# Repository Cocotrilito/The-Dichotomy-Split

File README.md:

# The -Dichotomy- Split

[Download Final Firmware](<BUILD FINAL FIRMWARE PICTURES ETC/FinalFirmware.zip>)

An Split keyboard, created to understand new things like matrix and wireless things, and also from the feeling of being split, Im trying to become someone new but im still stuck in this hole, A tool for the transition... a bridge out of the hole.

## The reason behind this project...
Initially I wanted to prove myself I could go a little more deeper, what I mean Is that I had already made a macropad as my first hackclub project 4 months ago, and the split keyboard was the logical step, when I started with KiCad Fusion and coding.
everything was really hard im not saying today it isnt, but compared to how much I struggled 4 months ago, I can proudly say I have learned, and not just a little, but A LOT, and as I am writing this, throught my headphones KUNGFUPANDA theme song is blasting my
ears, this is the same song I used to play back and back again 4 months ago, and you see 4 months ago I was lost (im still kinda but not as I was), I was heartbroken, and without an actual purpose, and I saw I video on my feed talking about blueprint, this made
me really curious, and I started learning, and now here I am, well I wanted to learn about ZMK in my macropad I only did the QMK firmware but I really wanted to tryout ZMK, and was really cool!, also I wanted to make the projects that I thought were impossible
and to the Isaac of 4 months ago... Thanks!, you have really changed your life, and to the future Isaac... How are you doing? was it all worth it?... thanks for reading if you did! <3

## zmk repo
[ZMK code](https://github.com/Cocotrilito/zmk-config)
## layout

## Schematic Overview

## PCB

<table>
  <tr>
    <td align="center"><br><b>PCB OVERVIEW</b></td>
    <td align="center"><br><b>Render</b></td>
    <td align="center"><br><b>PCB layout</b></td>
  </tr>
  <tr>
    <td align="center"><br><b>PCB Top</b></td>
    <td align="center"><br><b>PCB Back</b></td>
    <td></td>
  </tr>
</table>

## CAD Render

## BOM

| Name | Purpose | Qty | Total Cost (USD) | Link |
| :--- | :--- | :---: | :---: | :--- |
| **1N4148W SOD-123** | Efficiency for pins in matrix, also avoids ghosting | 1 (set) | $1.31 | [AliExpress](https://www.aliexpress.us/item/3256810466885186.html) |
| **XDA Profile PBT Keycaps** | Ergonomics and feel | 1 (set) | $11.83 | [AliExpress](https://www.aliexpress.us/item/3256810402164930.html) |
| **Outemu Silent Switches** | Mechanical input (Tactile/Silent) | 1 (set) | $7.55 | [AliExpress](https://www.aliexpress.us/item/3256811652574937.html) |
| **LEDs SK6812 MINI-E** | Per-key RGB lighting (WS2812B compatible) | 1 (set) | $4.83 | [AliExpress](https://www.aliexpress.us/item/3256810305129996.html) |
| **PCB Manufacturing** | Custom designed PCBs for the split layout | 1 (set) | $14.60 | [JLCPCB] |
| **Seeed Studio XIAO nRF52840** | Main microcontrollers with BLE for wireless | 2 | $37.98 | [Amazon](https://www.amazon.com/gp/product/B09T9VVQG7/) |

## SPECIAL THANKS!
Thanks for reading! made possible with [STASIS by HackClubbers](http://stasis.hackclub.com/)

## You might also like!
[Voyager Panel](https://github.com/Cocotrilito/Voyager-Panel)
[HALO-0](https://github.com/Cocotrilito/HALO-0)

## final thanks :3
By cocotrilo made with luv (THIS ONE WAS WITH philosophical meaning) keep the grind <3

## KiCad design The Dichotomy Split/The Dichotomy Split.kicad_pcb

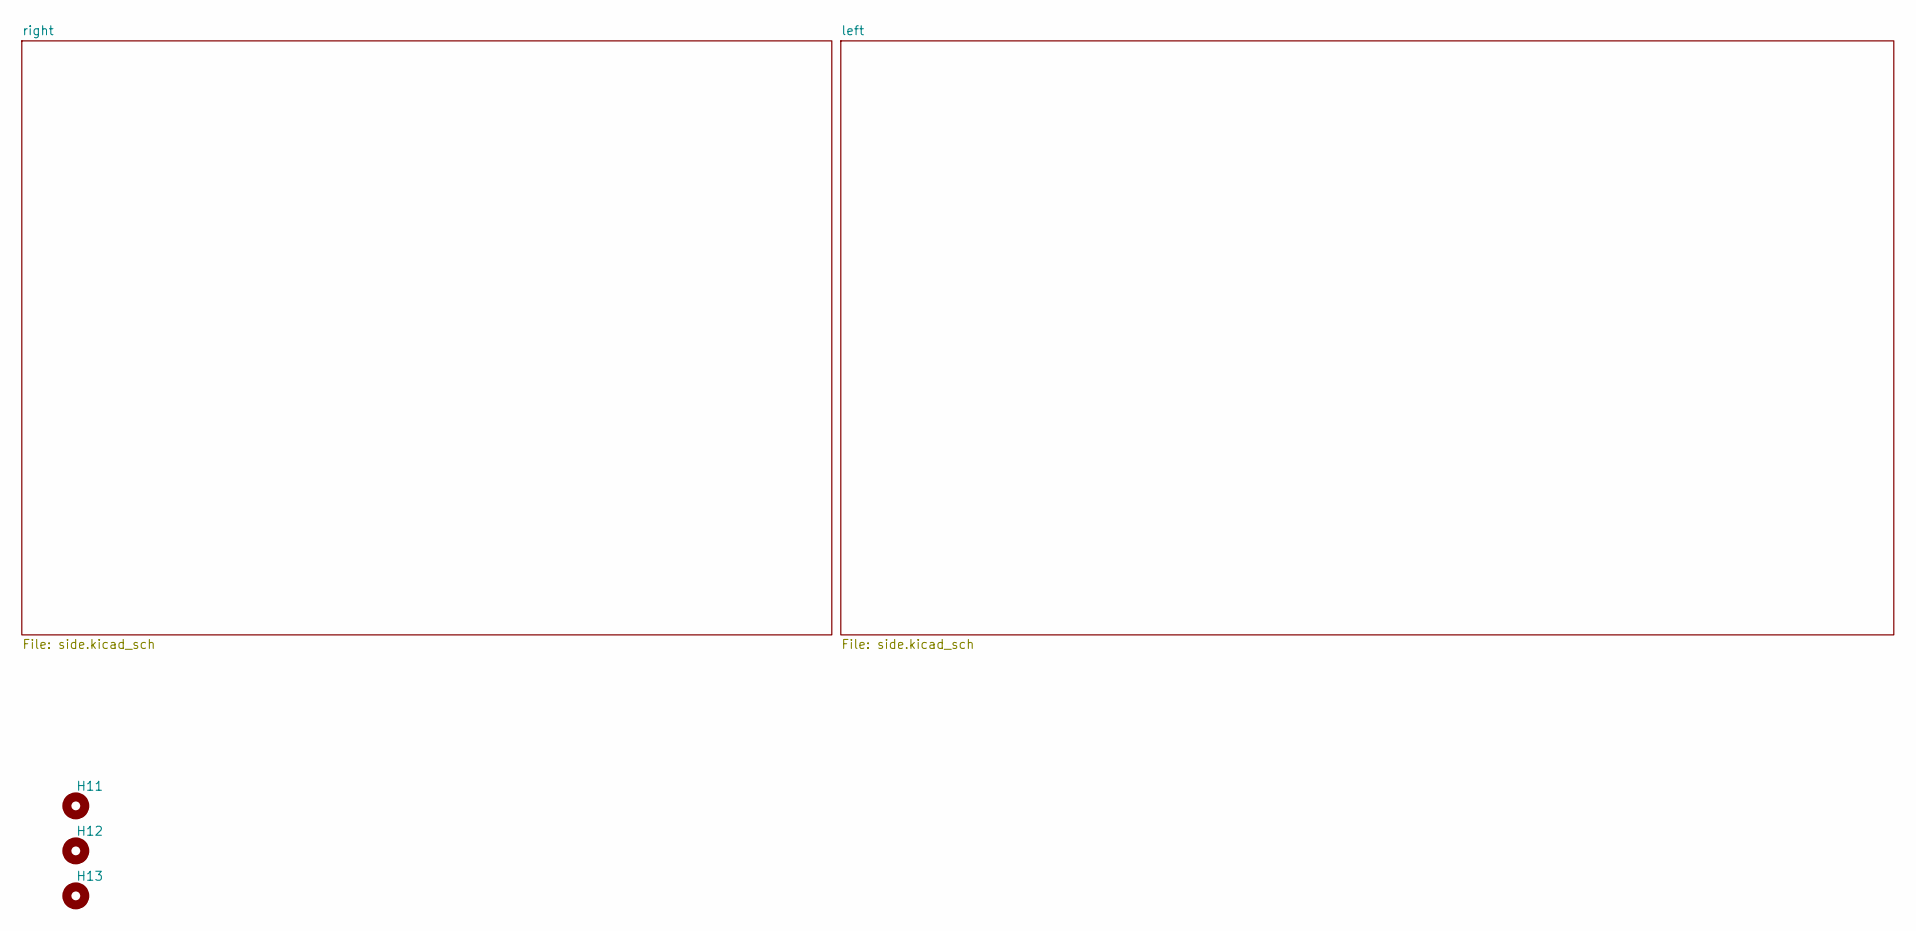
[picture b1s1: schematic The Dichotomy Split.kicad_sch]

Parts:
H11, H12, H13: MountingHole; mouse-bite-5mm-slot

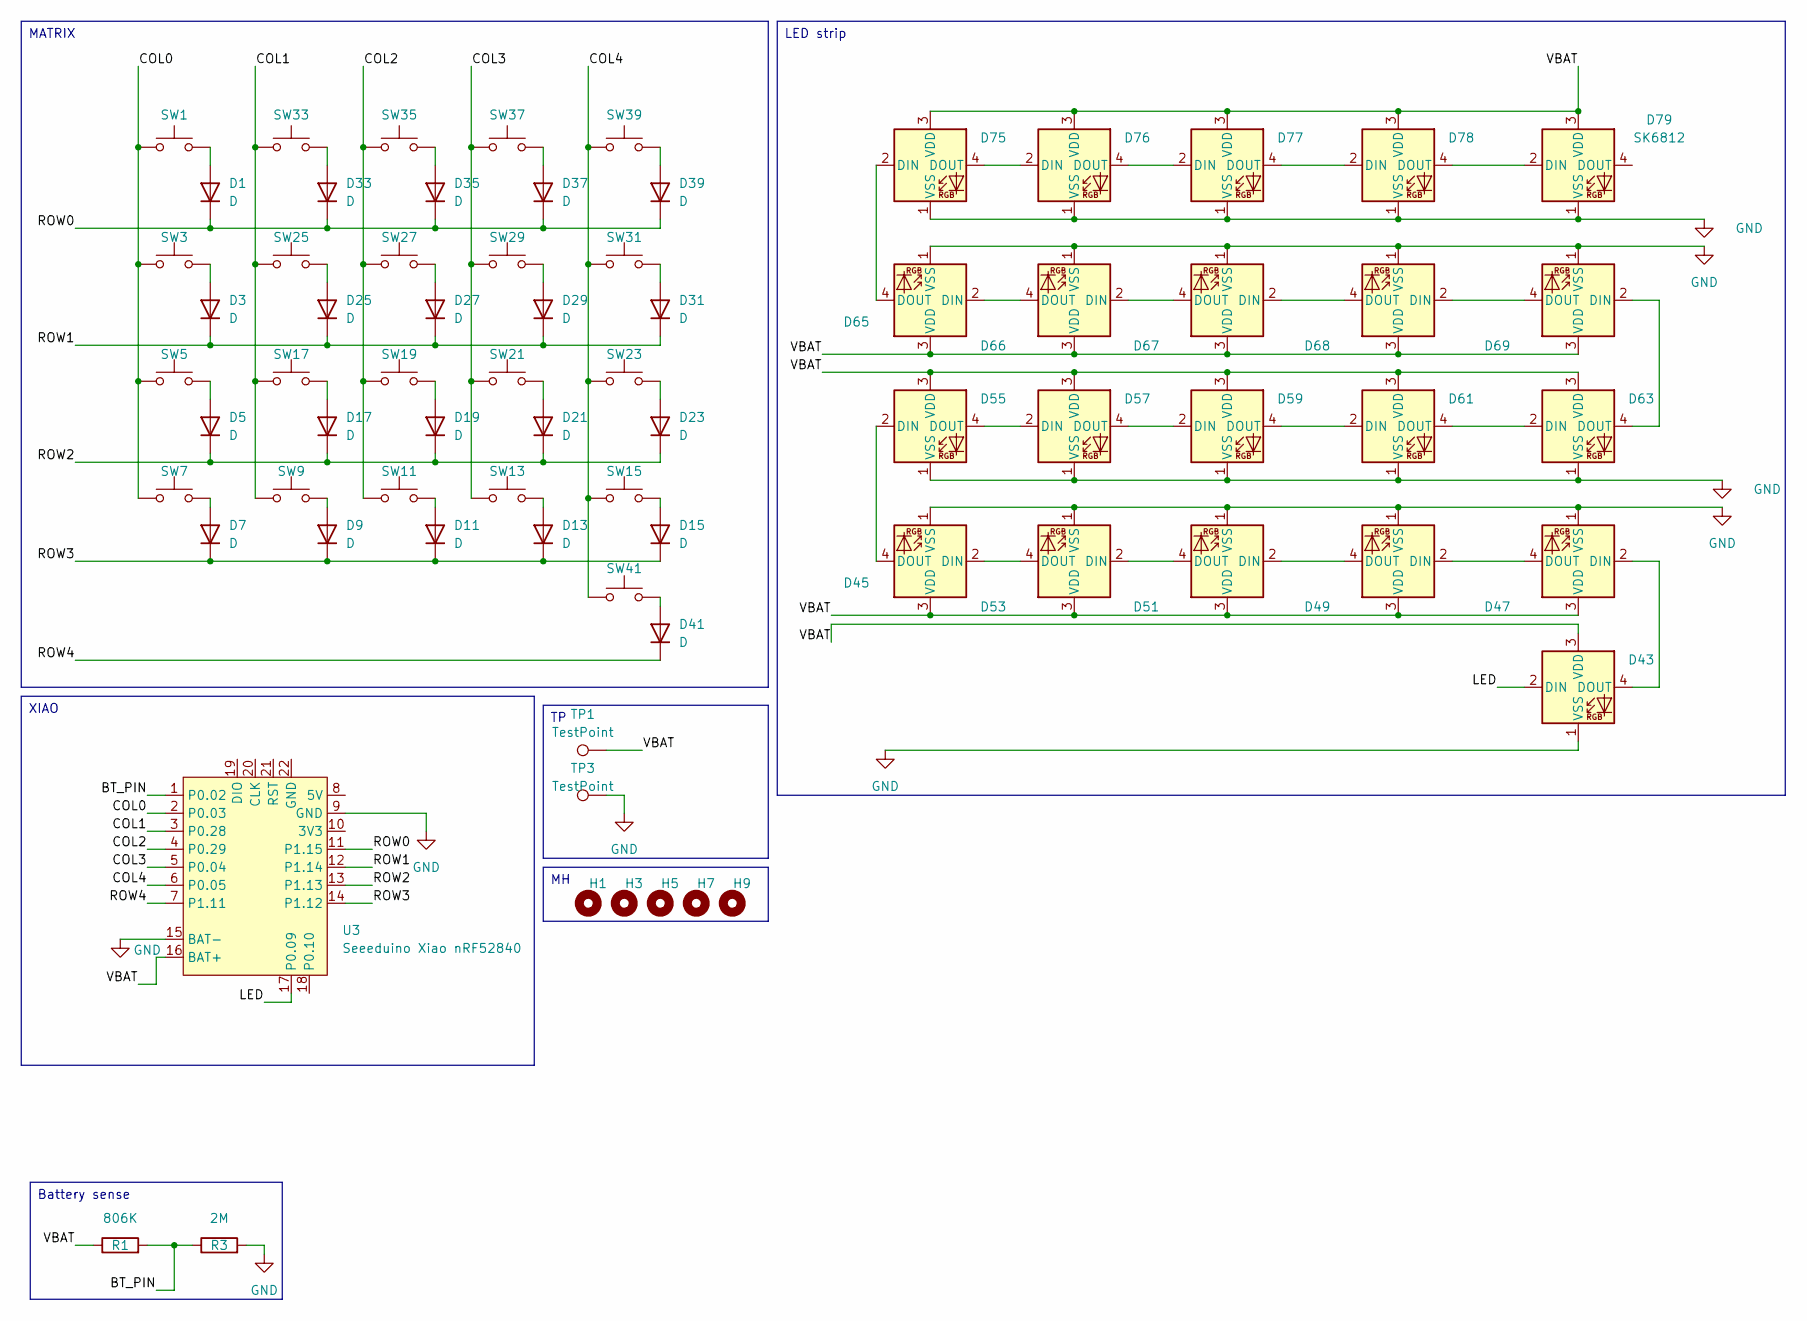
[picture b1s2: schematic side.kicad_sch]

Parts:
D1, D3, D5, D7, D9, D11, D13, D15, D17, D19, D21, D23, D25, D27, D29, D31, D33, D35, D37, D39, D41: D; D_SOD-123
D43, D45, D47, D49, D51, D53, D55, D57, D59, D61, D63, D65, D66, D67, D68, D69, D75, D76, D77, D78, D79: SK6812; LED_SK6812MINI-E_3.2x2.8mm_P1.5mm_ReverseMount
H1, H3, H5, H7, H9: MountingHole; MountingHole_3.2mm_M3_DIN965_Pad
R1: 806K; R_0805_2012Metric
R3: 2M; R_0805_2012Metric
SW1, SW3, SW5, SW7, SW9, SW11, SW13, SW15, SW17, SW19, SW21, SW23, SW25, SW27, SW29, SW31, SW33, SW35, SW37, SW39, SW41: SW_Push; SW_MX_1u
TP1, TP3: TestPoint; TestPoint_Pad_D2.0mm
U3: Seeeduino Xiao nRF52840; Xiao_nRF52840_ACH

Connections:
/right/BT_PIN: R1.2, R3.1, U3.1 (P0.02)
/right/COL0: SW1.1, SW3.1, SW5.1, SW7.1, U3.2 (P0.03)
/right/COL1: SW9.1, SW17.1, SW25.1, SW33.1, U3.3 (P0.28)
/right/COL2: SW11.1, SW19.1, SW27.1, SW35.1, U3.4 (P0.29)
/right/COL3: SW13.1, SW21.1, SW29.1, SW37.1, U3.5 (P0.04)
/right/COL4: SW15.1, SW23.1, SW31.1, SW39.1, SW41.1, U3.6 (P0.05)
/right/LED: D43.2 (DIN), U3.17 (P0.09)
/right/ROW0: D1.1 (K), D33.1 (K), D35.1 (K), D37.1 (K), D39.1 (K), U3.11 (P1.15)
/right/ROW1: D3.1 (K), D25.1 (K), D27.1 (K), D29.1 (K), D31.1 (K), U3.12 (P1.14)
/right/ROW2: D5.1 (K), D17.1 (K), D19.1 (K), D21.1 (K), D23.1 (K), U3.13 (P1.13)
/right/ROW3: D7.1 (K), D9.1 (K), D11.1 (K), D13.1 (K), D15.1 (K), U3.14 (P1.12)
/right/ROW4: D41.1 (K), U3.7 (P1.11)
/right/VBAT: D43.3 (VDD), D45.3 (VDD), D47.3 (VDD), D49.3 (VDD), D51.3 (VDD), D53.3 (VDD), D55.3 (VDD), D57.3 (VDD), D59.3 (VDD), D61.3 (VDD), D63.3 (VDD), D65.3 (VDD), D66.3 (VDD), D67.3 (VDD), D68.3 (VDD), D69.3 (VDD), D75.3 (VDD), D76.3 (VDD), D77.3 (VDD), D78.3 (VDD), D79.3 (VDD), R1.1, TP1.1 (1_1), U3.16 (BAT+)
GND: D43.1 (VSS), D45.1 (VSS), D47.1 (VSS), D49.1 (VSS), D51.1 (VSS), D53.1 (VSS), D55.1 (VSS), D57.1 (VSS), D59.1 (VSS), D61.1 (VSS), D63.1 (VSS), D65.1 (VSS), D66.1 (VSS), D67.1 (VSS), D68.1 (VSS), D69.1 (VSS), D75.1 (VSS), D76.1 (VSS), D77.1 (VSS), D78.1 (VSS), D79.1 (VSS), R3.2, TP3.1 (1_1), U3.9 (GND), U3.15 (BAT-); also elsewhere on the board
unnamed: D1.2 (A), SW1.2
unnamed: D3.2 (A), SW3.2
unnamed: D5.2 (A), SW5.2
unnamed: D7.2 (A), SW7.2
unnamed: D9.2 (A), SW9.2
unnamed: D11.2 (A), SW11.2
unnamed: D13.2 (A), SW13.2
unnamed: D15.2 (A), SW15.2
unnamed: D17.2 (A), SW17.2
unnamed: D19.2 (A), SW19.2
unnamed: D21.2 (A), SW21.2
unnamed: D23.2 (A), SW23.2
unnamed: D25.2 (A), SW25.2
unnamed: D27.2 (A), SW27.2
unnamed: D29.2 (A), SW29.2
unnamed: D31.2 (A), SW31.2
unnamed: D33.2 (A), SW33.2
unnamed: D35.2 (A), SW35.2
unnamed: D37.2 (A), SW37.2
unnamed: D39.2 (A), SW39.2
unnamed: D41.2 (A), SW41.2
unnamed: D43.4 (DOUT), D47.2 (DIN)
unnamed: D45.2 (DIN), D53.4 (DOUT)
unnamed: D45.4 (DOUT), D55.2 (DIN)
unnamed: D47.4 (DOUT), D49.2 (DIN)
unnamed: D49.4 (DOUT), D51.2 (DIN)
unnamed: D51.4 (DOUT), D53.2 (DIN)
unnamed: D55.4 (DOUT), D57.2 (DIN)
unnamed: D57.4 (DOUT), D59.2 (DIN)
unnamed: D59.4 (DOUT), D61.2 (DIN)
unnamed: D61.4 (DOUT), D63.2 (DIN)
unnamed: D63.4 (DOUT), D69.2 (DIN)
unnamed: D65.2 (DIN), D66.4 (DOUT)
unnamed: D65.4 (DOUT), D75.2 (DIN)
unnamed: D66.2 (DIN), D67.4 (DOUT)
unnamed: D67.2 (DIN), D68.4 (DOUT)
unnamed: D68.2 (DIN), D69.4 (DOUT)
unnamed: D75.4 (DOUT), D76.2 (DIN)
unnamed: D76.4 (DOUT), D77.2 (DIN)
unnamed: D77.4 (DOUT), D78.2 (DIN)
unnamed: D78.4 (DOUT), D79.2 (DIN)

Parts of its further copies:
D2, D4, D6, D8, D10, D12, D14, D16, D18, D20, D22, D24, D26, D28, D30, D32, D34, D36, D38, D40, D42: D; D_SOD-123
D44, D46, D48, D50, D52, D54, D56, D58, D60, D62, D64, D70, D71, D72, D73, D74, D80, D81, D82, D83, D84: SK6812; LED_SK6812MINI-E_3.2x2.8mm_P1.5mm_ReverseMount
H2, H4, H6: MountingHole; MountingHole_3.2mm_M3_DIN965_Pad
R2: 806K; R_0805_2012Metric
R4: 2M; R_0805_2012Metric
SW2, SW4, SW6, SW8, SW10, SW12, SW14, SW16, SW18, SW20, SW22, SW24, SW26, SW28, SW30, SW32, SW34, SW36, SW38, SW40, SW42: SW_Push; SW_MX_1u
TP2, TP4: TestPoint; TestPoint_Pad_D2.0mm
U4: Seeeduino Xiao nRF52840; Xiao_nRF52840_ACH

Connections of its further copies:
/left/BT_PIN: R2.2, R4.1, U4.1 (P0.02)
/left/COL0: SW2.1, SW4.1, SW6.1, SW8.1, U4.2 (P0.03)
/left/COL1: SW10.1, SW18.1, SW26.1, SW34.1, U4.3 (P0.28)
/left/COL2: SW12.1, SW20.1, SW28.1, SW36.1, U4.4 (P0.29)
/left/COL3: SW14.1, SW22.1, SW30.1, SW38.1, U4.5 (P0.04)
/left/COL4: SW16.1, SW24.1, SW32.1, SW40.1, SW42.1, U4.6 (P0.05)
/left/LED: D44.2 (DIN), U4.17 (P0.09)
/left/ROW0: D2.1 (K), D34.1 (K), D36.1 (K), D38.1 (K), D40.1 (K), U4.11 (P1.15)
/left/ROW1: D4.1 (K), D26.1 (K), D28.1 (K), D30.1 (K), D32.1 (K), U4.12 (P1.14)
/left/ROW2: D6.1 (K), D18.1 (K), D20.1 (K), D22.1 (K), D24.1 (K), U4.13 (P1.13)
/left/ROW3: D8.1 (K), D10.1 (K), D12.1 (K), D14.1 (K), D16.1 (K), U4.14 (P1.12)
/left/ROW4: D42.1 (K), U4.7 (P1.11)
/left/VBAT: D44.3 (VDD), D46.3 (VDD), D48.3 (VDD), D50.3 (VDD), D52.3 (VDD), D54.3 (VDD), D56.3 (VDD), D58.3 (VDD), D60.3 (VDD), D62.3 (VDD), D64.3 (VDD), D70.3 (VDD), D71.3 (VDD), D72.3 (VDD), D73.3 (VDD), D74.3 (VDD), D80.3 (VDD), D81.3 (VDD), D82.3 (VDD), D83.3 (VDD), D84.3 (VDD), R2.1, TP2.1 (1_1), U4.16 (BAT+)
GND: D44.1 (VSS), D46.1 (VSS), D48.1 (VSS), D50.1 (VSS), D52.1 (VSS), D54.1 (VSS), D56.1 (VSS), D58.1 (VSS), D60.1 (VSS), D62.1 (VSS), D64.1 (VSS), D70.1 (VSS), D71.1 (VSS), D72.1 (VSS), D73.1 (VSS), D74.1 (VSS), D80.1 (VSS), D81.1 (VSS), D82.1 (VSS), D83.1 (VSS), D84.1 (VSS), R4.2, TP4.1 (1_1), U4.9 (GND), U4.15 (BAT-); also elsewhere on the board
unnamed: D2.2 (A), SW2.2
unnamed: D4.2 (A), SW4.2
unnamed: D6.2 (A), SW6.2
unnamed: D8.2 (A), SW8.2
unnamed: D10.2 (A), SW10.2
unnamed: D12.2 (A), SW12.2
unnamed: D14.2 (A), SW14.2
unnamed: D16.2 (A), SW16.2
unnamed: D18.2 (A), SW18.2
unnamed: D20.2 (A), SW20.2
unnamed: D22.2 (A), SW22.2
unnamed: D24.2 (A), SW24.2
unnamed: D26.2 (A), SW26.2
unnamed: D28.2 (A), SW28.2
unnamed: D30.2 (A), SW30.2
unnamed: D32.2 (A), SW32.2
unnamed: D34.2 (A), SW34.2
unnamed: D36.2 (A), SW36.2
unnamed: D38.2 (A), SW38.2
unnamed: D40.2 (A), SW40.2
unnamed: D42.2 (A), SW42.2
unnamed: D44.4 (DOUT), D48.2 (DIN)
unnamed: D46.2 (DIN), D54.4 (DOUT)
unnamed: D46.4 (DOUT), D56.2 (DIN)
unnamed: D48.4 (DOUT), D50.2 (DIN)
unnamed: D50.4 (DOUT), D52.2 (DIN)
unnamed: D52.4 (DOUT), D54.2 (DIN)
unnamed: D56.4 (DOUT), D58.2 (DIN)
unnamed: D58.4 (DOUT), D60.2 (DIN)
unnamed: D60.4 (DOUT), D62.2 (DIN)
unnamed: D62.4 (DOUT), D64.2 (DIN)
unnamed: D64.4 (DOUT), D74.2 (DIN)
unnamed: D70.2 (DIN), D71.4 (DOUT)
unnamed: D70.4 (DOUT), D80.2 (DIN)
unnamed: D71.2 (DIN), D72.4 (DOUT)
unnamed: D72.2 (DIN), D73.4 (DOUT)
unnamed: D73.2 (DIN), D74.4 (DOUT)
unnamed: D80.4 (DOUT), D81.2 (DIN)
unnamed: D81.4 (DOUT), D82.2 (DIN)
unnamed: D82.4 (DOUT), D83.2 (DIN)
unnamed: D83.4 (DOUT), D84.2 (DIN)

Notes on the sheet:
MATRIX
LED strip
XIAO
Battery sense

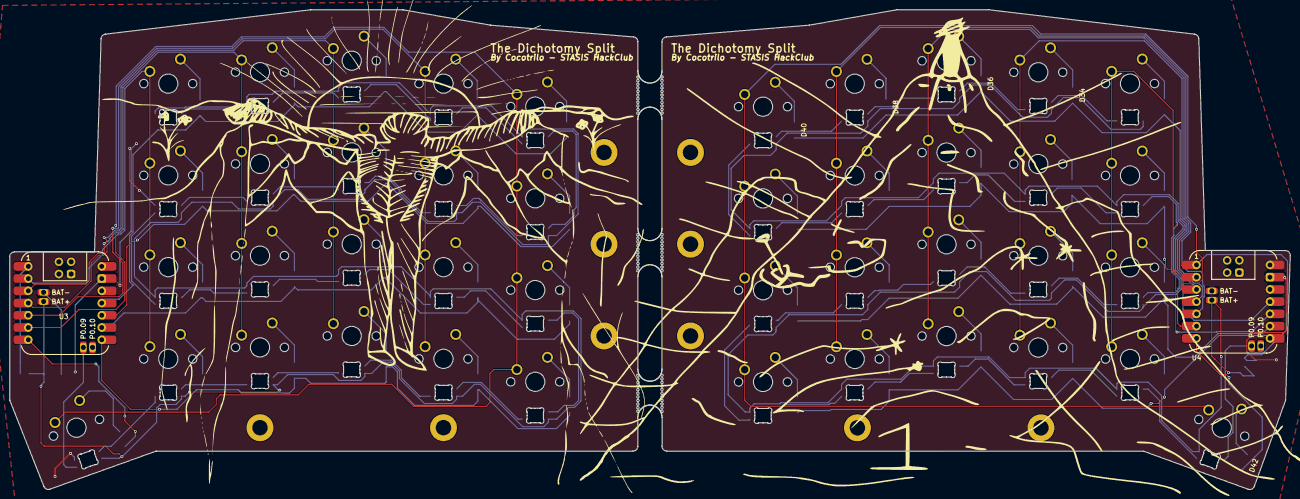
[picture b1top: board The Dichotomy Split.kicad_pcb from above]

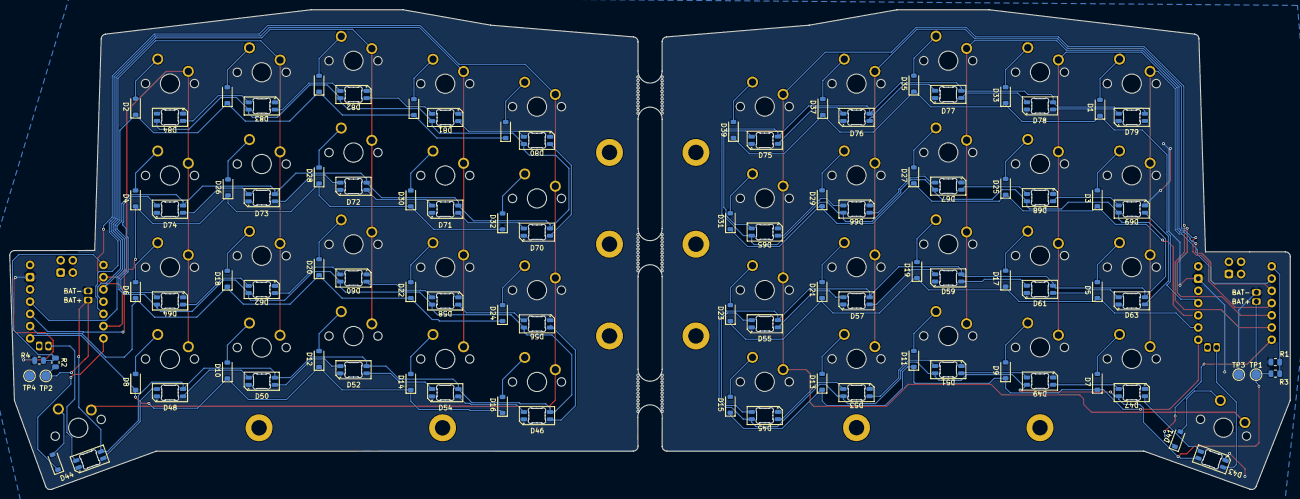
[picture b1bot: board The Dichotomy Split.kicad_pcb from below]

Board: 2 copper layers, 265.8 x 99.5 mm, 149 parts (92 on the bottom side), 109 nets.

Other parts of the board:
H1#2, H3#2: MountingHole; MountingHole_3.2mm_M3_DIN965_Pad

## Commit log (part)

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2026-04-26 SETUP LIBS
2026-04-27 Schematic AND pcb finished!
2026-04-27 pictures CAD BOM GERBERS ZMK FIRMWARE
2026-04-28 added final images
2026-04-28 Create README.md for -Dichotomy- Split keyboard project
    Added detailed project overview, including reasons for creation, schematic, PCB images, BOM, and acknowledgments.
2026-04-28 Added final image
2026-04-28 Add PCB Back image to README
2026-04-28 Revise BOM section with detailed item descriptions
2026-04-28 Update README with ZMK info and layout image
    Added a section for ZMK repository and layout image.
